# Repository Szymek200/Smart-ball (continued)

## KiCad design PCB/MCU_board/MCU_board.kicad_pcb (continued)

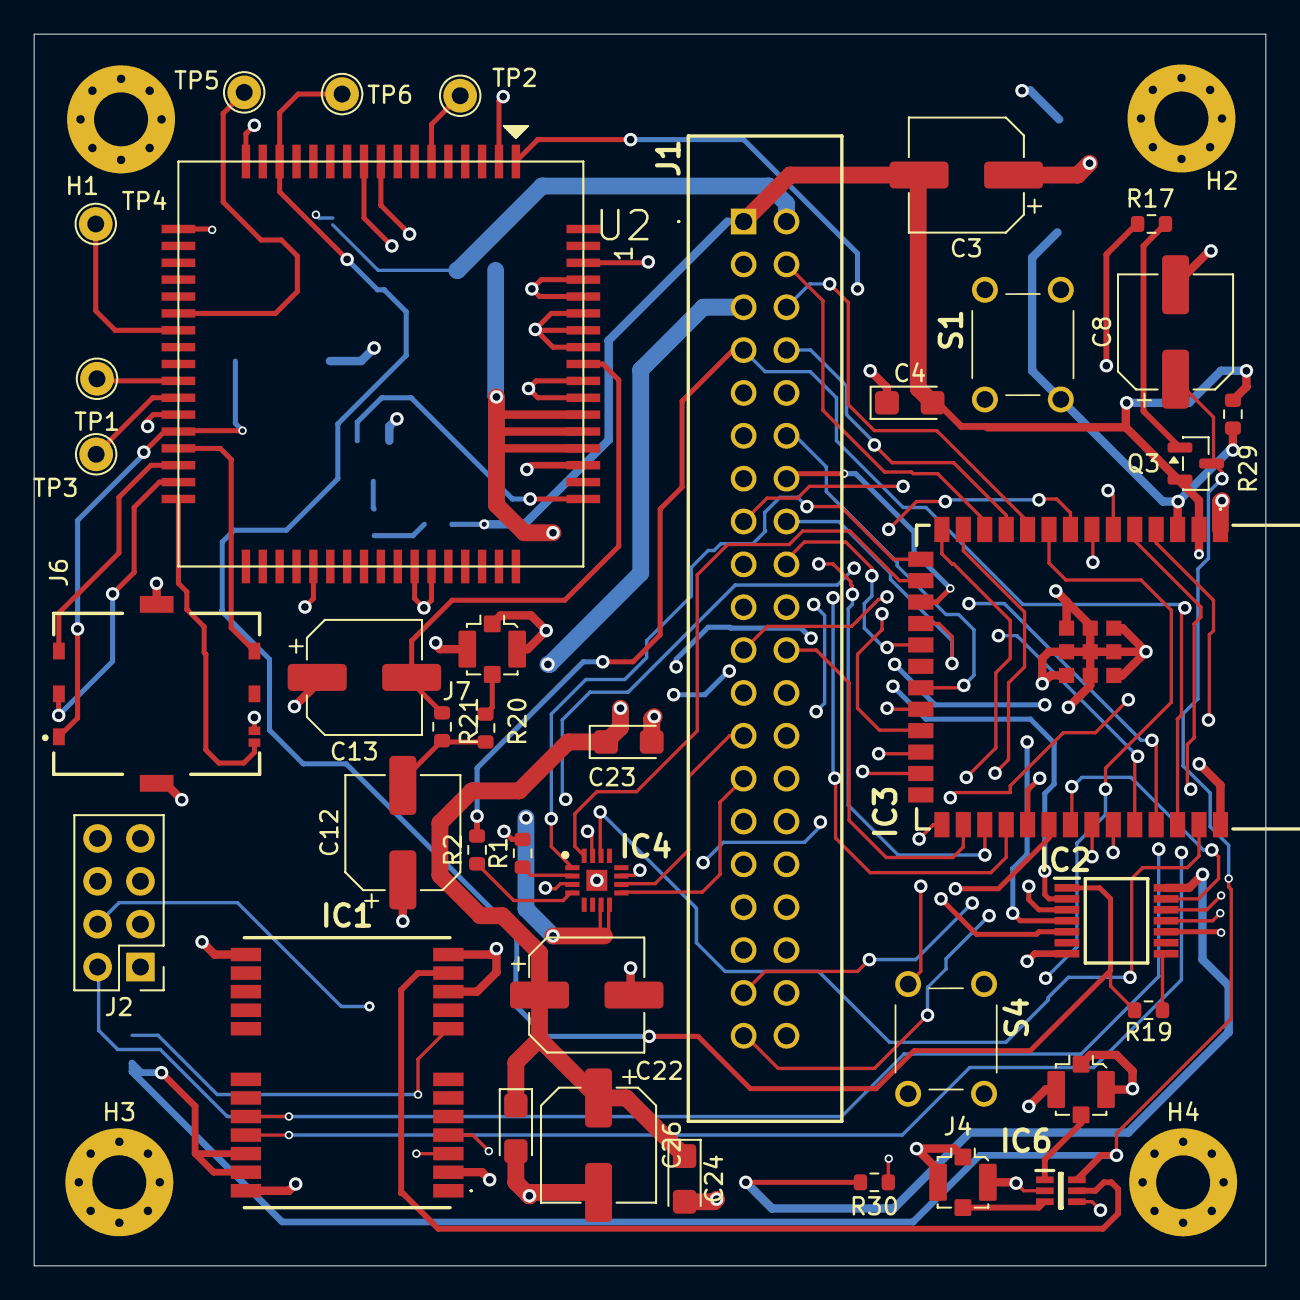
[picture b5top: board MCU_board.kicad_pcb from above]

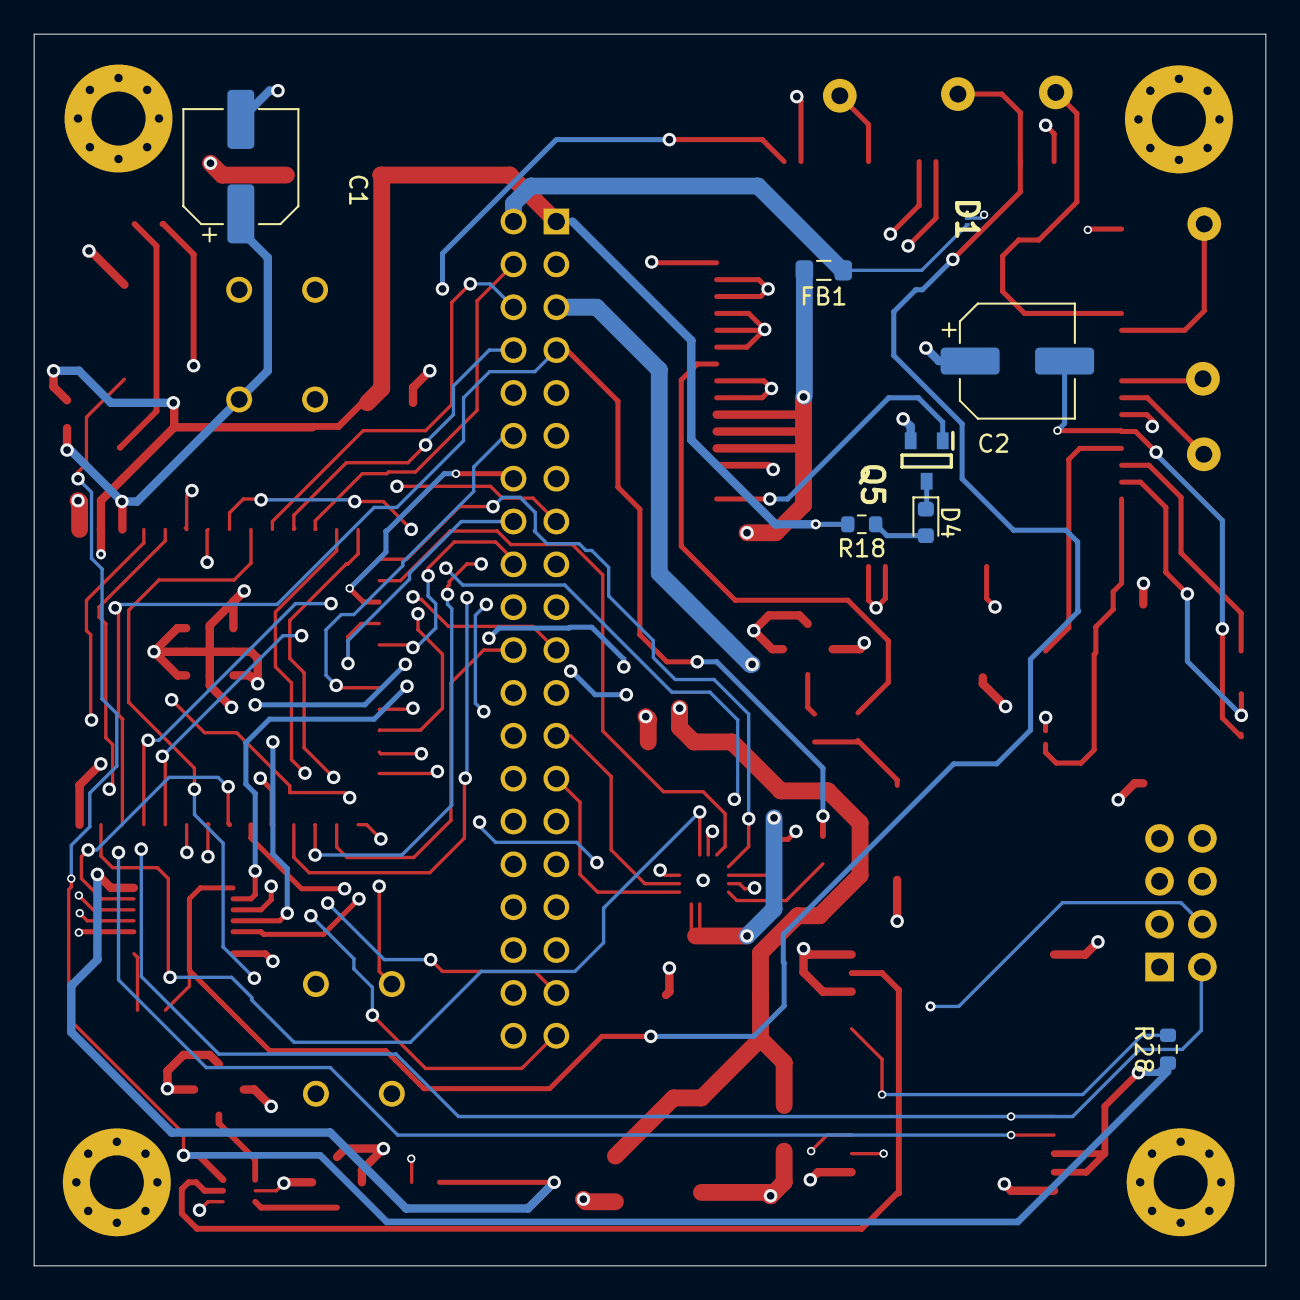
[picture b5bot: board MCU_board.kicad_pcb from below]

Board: 4 copper layers, 73.0 x 73.0 mm, 51 parts (8 on the bottom side), 72 nets.

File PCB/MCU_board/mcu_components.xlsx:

Designator | Footprint | Quantity | Value | LCSC Part #
C1, C26 | C_Disc_D5.0mm_W2.5mm_P2.50mm | 2 | 1μF
C12, C13 | C_Disc_D5.0mm_W2.5mm_P2.50mm | 2 | 0F
C2, C3 | C_Disc_D5.0mm_W2.5mm_P2.50mm | 2 | 100nF
C22 | C_Disc_D5.0mm_W2.5mm_P2.50mm | 1 | 1000nF
C23 | CP_Radial_Tantal_D5.0mm_P2.50mm | 1 | 1000µF
C24, C25 | CP_Radial_Tantal_D5.0mm_P2.50mm | 2 | 100µF
C4 | CP_Radial_Tantal_D5.0mm_P2.50mm | 1 | 1μF
C8 | C_Disc_D5.0mm_W2.5mm_P2.50mm | 1 | 100 nF
D1 | PMEG3005AESFYL | 1 | PESD5V0C1BSFYL
D4 | D_DO-41_SOD81_P7.62mm_Horizontal | 1 | LED
FB1 | 805 | 1 | 280Ω
IC1 | NEOF10N00B | 1 | NEO-F10N-00B
IC2 | SOP65P640X120-14N | 1 | TXB0104PWR
IC3 | ESP32S3WROOM1N4R8 | 1 | ESP32-S3-WROOM-1-N4R8
IC6 | SOT65P210X110-6N | 1 | 4259-63
IC8 | QFN50P300X300X80-17N | 1 | MAX98357AETE+T
J1 | DS101340SSIB1B0 | 1 | DS1013-40SSIB1-B-0
J4 | U.FL_Molex_MCRF_73412-0110_Vertical | 1 | FXP612 (u.FL) 2
J5, J7 | U.FL_Molex_MCRF_73412-0110_Vertical | 2 | FXP612 (u.FL) 1
J6 | GCT_SIM8055-6-1-14-00-A | 1 | SIM8055-6-1-14-00-A
Q3 | SOT95P237X112-3N | 1 | Si2323DDS-T1-GE3
Q5 | SOT95P240X120-3N | 1 | BSS138
R16, R26 | R_Axial_DIN0207_L6.3mm_D2.5mm_P7.62mm_Horizontal | 2 | 100kΩ
R17, R19, R28, R29, R30 | R_Axial_DIN0207_L6.3mm_D2.5mm_P7.62mm_Horizontal | 5 | 10kΩ
R18 | R_Axial_DIN0207_L6.3mm_D2.5mm_P7.62mm_Horizontal | 1 | 330Ω
R20, R21 | R_Axial_DIN0207_L6.3mm_D2.5mm_P7.62mm_Horizontal | 2 | 0Ω
S1, S4 | 18259106 | 2 | 1825910-6
TP1 | TestPoint_THTPad_D2.0mm_Drill1.0mm | 1 | USB_DP
TP2 | TestPoint_THTPad_D2.0mm_Drill1.0mm | 1 | BOOT_CFG
TP3 | TestPoint_THTPad_D2.0mm_Drill1.0mm | 1 | USB_DM
TP4 | TestPoint_THTPad_D2.0mm_Drill1.0mm | 1 | USB_VBUS
TP5 | TestPoint_THTPad_D2.0mm_Drill1.0mm | 1 | MDM_LOG_TX
TP6 | TestPoint_THTPad_D2.0mm_Drill1.0mm | 1 | TestPoint
U2 | SIM7000G | 1 | SIM7000G

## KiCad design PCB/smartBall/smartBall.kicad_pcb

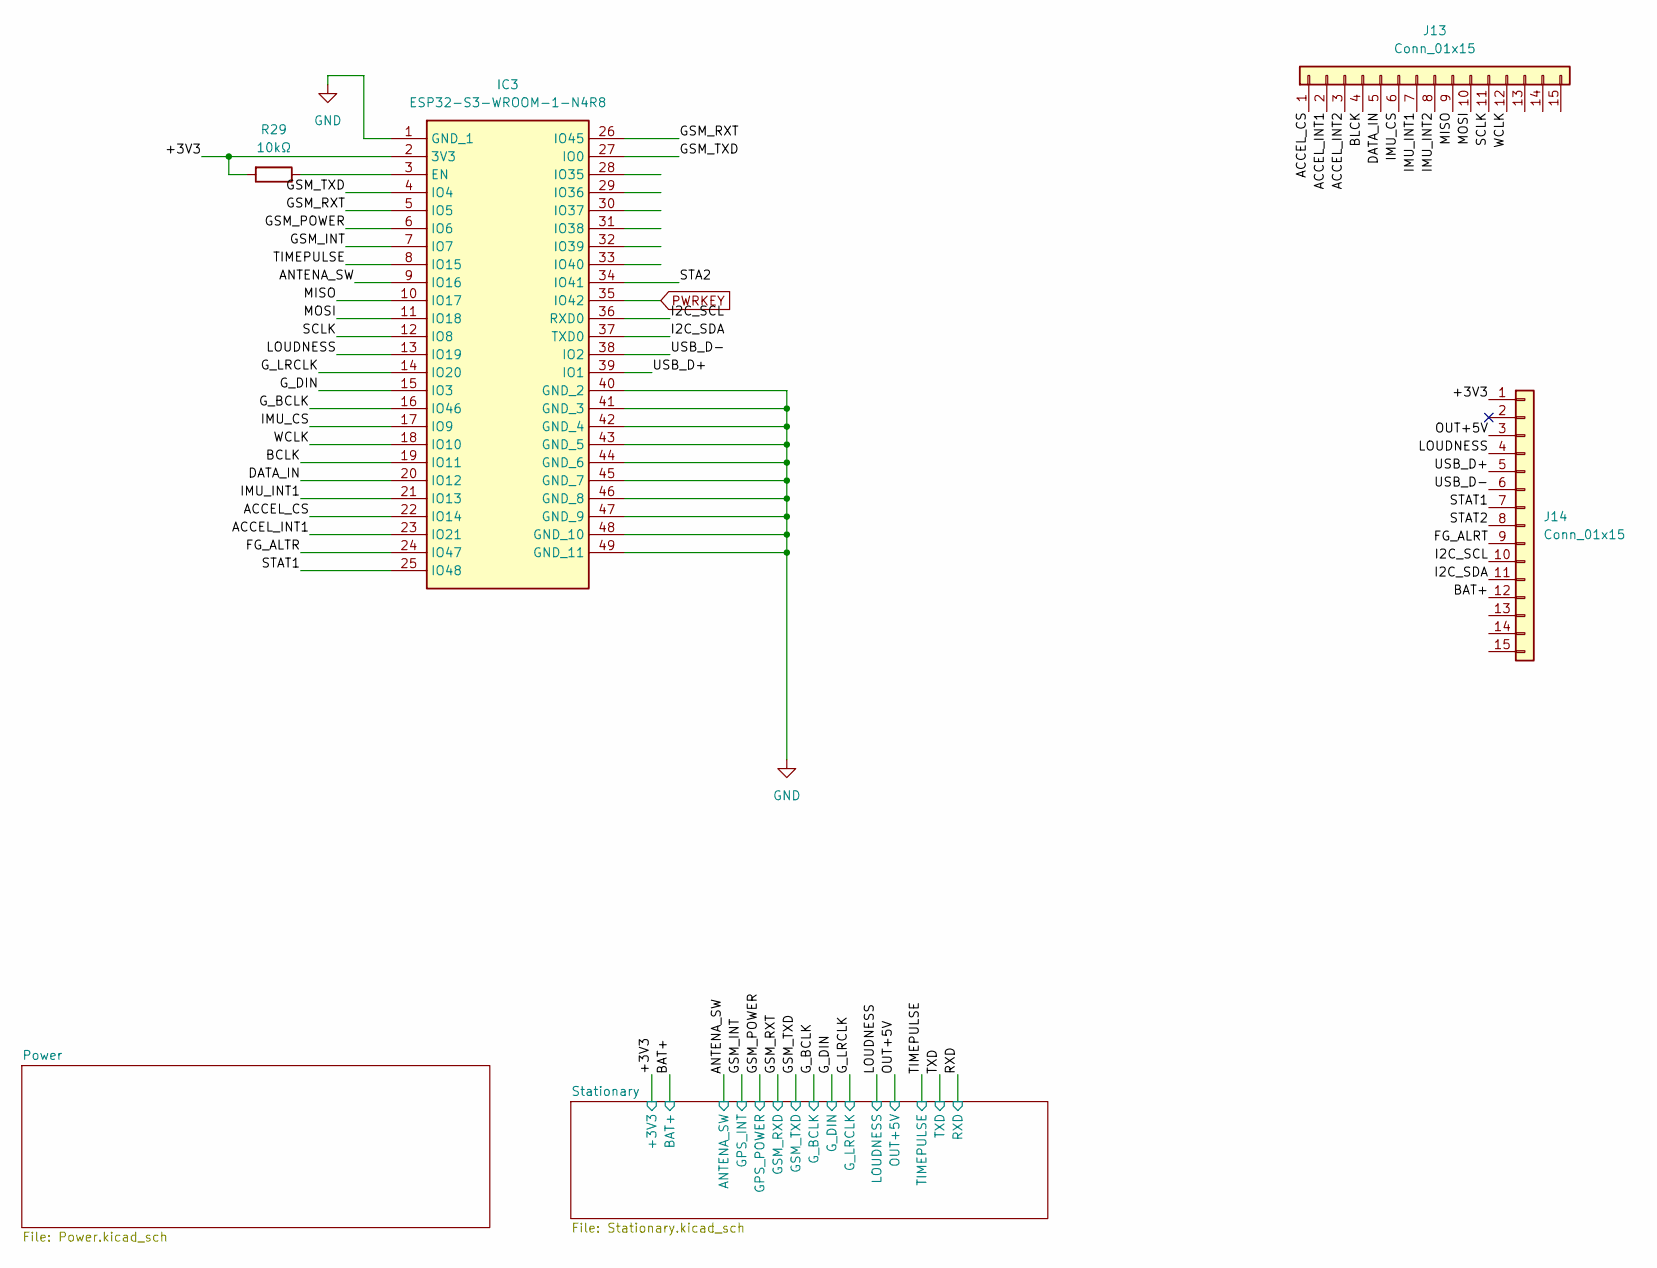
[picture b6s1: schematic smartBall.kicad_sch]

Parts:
IC3: ESP32-S3-WROOM-1-N4R8; ESP32S3WROOM1N4R8; Mouser Part Number 356-ESP32S3WROM1N4R8
J13, J14: Conn_01x15; PinHeader_1x15_P2.54mm_Vertical
R29: 10kΩ; R_Axial_DIN0207_L6.3mm_D2.5mm_P7.62mm_Horizontal

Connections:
/+3V3: IC3.2 (3V3), J14.1, R29.2; also elsewhere on the board
/ACCEL_CS: IC3.22 (IO14), J13.1
/ACCEL_INT1: IC3.23 (IO21), J13.2
/ACCEL_INT2: IC3.28 (IO35), J13.3
/ANTENA_SW: IC3.9 (IO16); also elsewhere on the board
/BAT+: J14.12
/DATA_IN: IC3.20 (IO12), J13.5
/GSM_INT: IC3.7 (IO7); also elsewhere on the board
/GSM_POWER: IC3.6 (IO6); also elsewhere on the board
/G_BCLK: IC3.16 (IO46); also elsewhere on the board
/G_DIN: IC3.15 (IO3); also elsewhere on the board
/G_LRCLK: IC3.14 (IO20); also elsewhere on the board
/I2C_SCL: IC3.36 (RXD0), J14.10
/I2C_SDA: IC3.37 (TXD0), J14.11
/IMU_CS: IC3.17 (IO9), J13.6
/IMU_INT1: IC3.21 (IO13), J13.7
/IMU_INT2: IC3.29 (IO36), J13.8
/LOUDNESS: IC3.13 (IO19), J14.4; also elsewhere on the board
/MISO: IC3.10 (IO17), J13.9
/MOSI: IC3.11 (IO18), J13.10
/OUT+5V: J14.3; also elsewhere on the board
/PWRKEY: IC3.31 (IO38); also elsewhere on the board
/SCLK: IC3.12 (IO8), J13.11
/STAT1: IC3.25 (IO48), J14.7
/STATUS: IC3.32 (IO39); also elsewhere on the board
/TIMEPULSE: IC3.8 (IO15); also elsewhere on the board
/TS/CTRL: IC3.30 (IO37), J14.2
/USB_D+: IC3.39 (IO1), J14.5
/USB_D-: IC3.38 (IO2), J14.6
/WCLK: IC3.18 (IO10), J13.12
GND: IC3.1 (GND_1), IC3.40 (GND_2), IC3.41 (GND_3), IC3.42 (GND_4), IC3.43 (GND_5), IC3.44 (GND_6), IC3.45 (GND_7), IC3.46 (GND_8), IC3.47 (GND_9), IC3.48 (GND_10), IC3.49 (GND_11); also elsewhere on the board
unnamed: IC3.3 (EN), R29.1

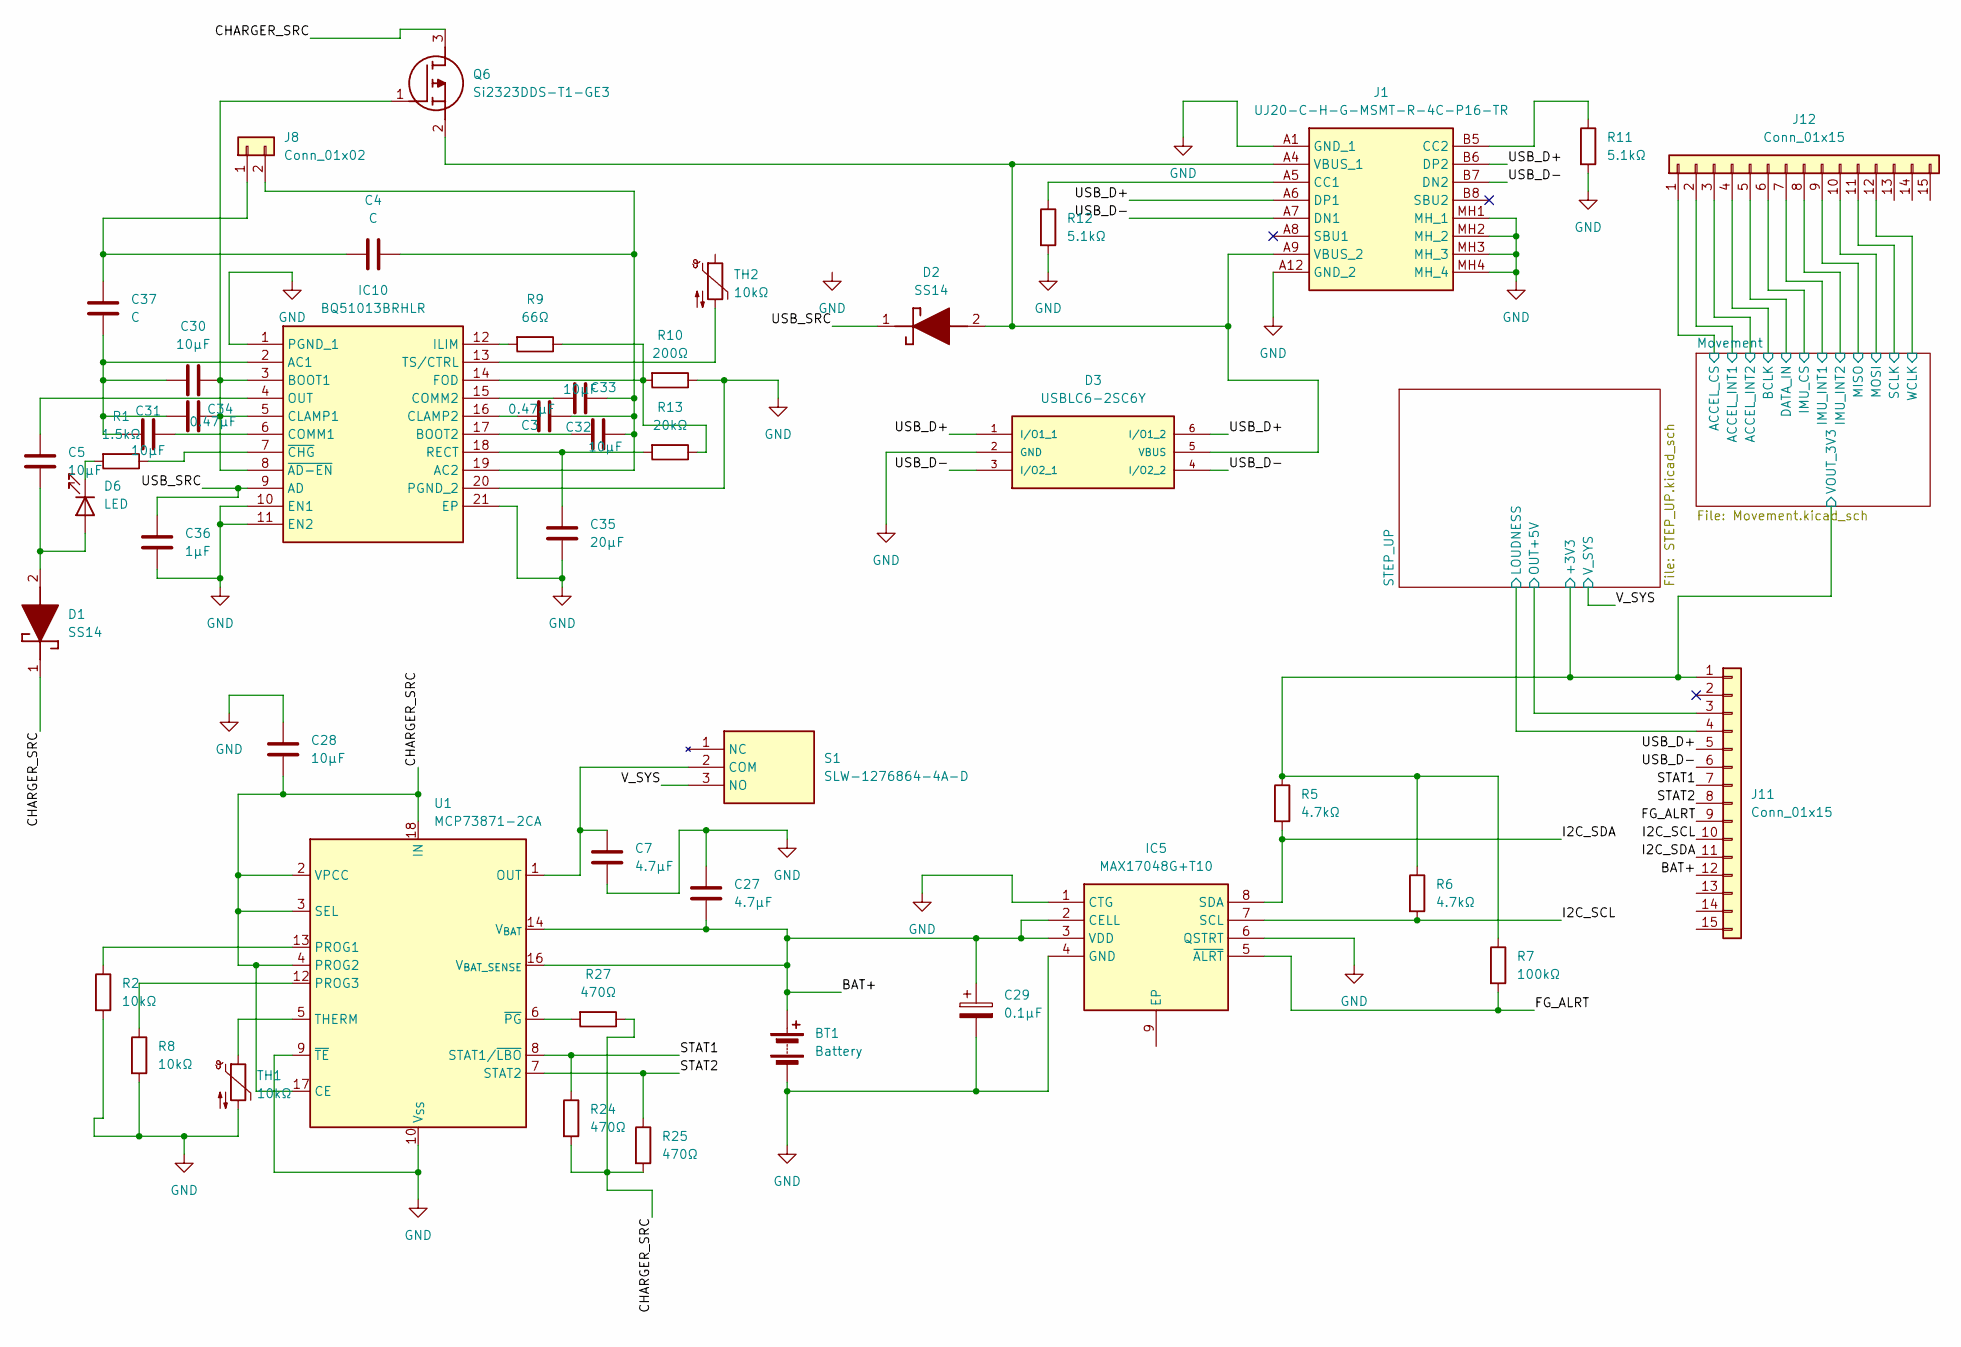
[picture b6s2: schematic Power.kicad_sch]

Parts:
BT1: Battery; SolderWire-0.75sqmm_1x02_P4.8mm_D1.25mm_OD2.3mm
C3, C34: 0.47µF; CP_Radial_Tantal_D5.0mm_P2.50mm
C4, C37: C; CP_Radial_Tantal_D5.0mm_P2.50mm
C5, C28, C30, C31, C32, C33: 10µF; CP_Radial_Tantal_D5.0mm_P2.50mm
C7, C27: 4.7µF; CP_Radial_Tantal_D5.0mm_P2.50mm
C29: 0.1µF; CP_Radial_Tantal_D5.0mm_P2.50mm
C35: 20µF; CP_Radial_Tantal_D5.0mm_P2.50mm
C36: 1µF; CP_Radial_Tantal_D5.0mm_P2.50mm
D1, D2: SS14; DIOM5227X270N; Mouser Part Number 512-SS14
D3: USBLC6-2SC6Y; SOT95P280X145-6N; MOUSER_PART_NUMBER 511-USBLC6-2SC6Y
D6: LED; D_DO-41_SOD81_P7.62mm_Horizontal
IC5: MAX17048G+T10; SON50P200X200X80-9N-D; Mouser Part Number 700-MAX17048G+T10
IC10: BQ51013BRHLR; BQ51050BRHLR; Mouser Part Number 595-BQ51013BRHLR
J1: UJ20-C-H-G-MSMT-R-4C-P16-TR; UJ20CHGMSMTR4CP16TR; Manufacturer_Part_Number UJ20-C-H-G-MSMT-R-4C-P16-TR
J8: Conn_01x02; PinHeader_1x02_P2.54mm_Vertical
J11, J12: Conn_01x15; PinHeader_1x15_P2.54mm_Vertical
Q6: Si2323DDS-T1-GE3; SOT95P237X112-3N; Mouser Part Number 78-SI2323DDS-T1-GE3
R1: 1.5kΩ; R_Axial_DIN0207_L6.3mm_D2.5mm_P7.62mm_Horizontal
R2, R8: 10kΩ; R_Axial_DIN0207_L6.3mm_D2.5mm_P7.62mm_Horizontal
R5, R6: 4.7kΩ; R_Axial_DIN0207_L6.3mm_D2.5mm_P7.62mm_Horizontal
R7: 100kΩ; R_Axial_DIN0207_L6.3mm_D2.5mm_P7.62mm_Horizontal
R9: 66Ω; R_Axial_DIN0207_L6.3mm_D2.5mm_P7.62mm_Horizontal
R10: 200Ω; R_Axial_DIN0207_L6.3mm_D2.5mm_P7.62mm_Horizontal
R11, R12: 5.1kΩ; R_Axial_DIN0207_L6.3mm_D2.5mm_P7.62mm_Horizontal
R13: 20kΩ; R_Axial_DIN0207_L6.3mm_D2.5mm_P7.62mm_Horizontal
R24, R25, R27: 470Ω; R_Axial_DIN0207_L6.3mm_D2.5mm_P7.62mm_Horizontal
S1: SLW-1276864-4A-D; SLW12768644AD; Mouser Part Number 179-SLW-1276864-4A-D
TH1, TH2: 10kΩ; R_Axial_DIN0207_L6.3mm_D2.5mm_P7.62mm_Horizontal
U1: MCP73871-2CA; QFN-20-1EP_4x4mm_P0.5mm_EP2.5x2.5mm

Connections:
/Power/BAT+: BT1.1 (+), C27.2, C29.1, IC5.2 (CELL), IC5.3 (VDD), J11.12, U1.14 (V_{BAT}), U1.15 (V_{BAT}), U1.16 (V_{BAT_SENSE})
/Power/CHARGER_SRC: C28.2, D1.1 (K), Q6.3 (D), R24.2, R25.2, R27.1, U1.2 (VPCC), U1.3 (SEL), U1.4 (PROG2), U1.17 (CE), U1.18 (IN), U1.19 (IN)
/Power/FG_ALRT: IC5.5 (~ALRT), J11.9, R7.2
/Power/I2C_SCL: IC5.7 (SCL), J11.10, R6.2
/Power/I2C_SDA: IC5.8 (SDA), J11.11, R5.2
/Power/Movement/ACCEL_CS: J12.1; also elsewhere on the board
/Power/Movement/ACCEL_INT1: J12.2; also elsewhere on the board
/Power/Movement/ACCEL_INT2: J12.3; also elsewhere on the board
/Power/Movement/BCLK: J12.4; also elsewhere on the board
/Power/Movement/DATA_IN: J12.5; also elsewhere on the board
/Power/Movement/IMU_CS: J12.6; also elsewhere on the board
/Power/Movement/IMU_INT1: J12.7; also elsewhere on the board
/Power/Movement/IMU_INT2: J12.8; also elsewhere on the board
/Power/Movement/MISO: J12.9; also elsewhere on the board
/Power/Movement/MOSI: J12.10; also elsewhere on the board
/Power/Movement/SCLK: J12.11; also elsewhere on the board
/Power/Movement/VOUT_3V3: J11.1, R5.1, R6.1, R7.1; also elsewhere on the board
/Power/Movement/WCLK: J12.12; also elsewhere on the board
/Power/STAT1: J11.7, R24.1, U1.8 (STAT1/~LBO)
/Power/STAT2: J11.8, R25.1, U1.7 (STAT2)
/Power/STEP_UP/LOUDNESS: J11.4; also elsewhere on the board
/Power/STEP_UP/OUT+5V: J11.3; also elsewhere on the board
/Power/USB_D+: D3.1 (I/O1_1), D3.6 (I/O1_2), J1.A6 (DP1), J1.B6 (DP2), J11.5
/Power/USB_D-: D3.3 (I/O2_1), D3.4 (I/O2_2), J1.A7 (DN1), J1.B7 (DN2), J11.6
/Power/USB_SRC: C36.1, D2.1 (K), IC10.9 (AD)
/Power/V_SYS: S1.3 (NO); also elsewhere on the board
GND: BT1.2 (-), C7.2, C27.1, C28.1, C29.2, C35.2, C36.2, D3.2 (GND), IC5.1 (CTG), IC5.4 (GND), IC5.6 (QSTRT), IC5.9 (EP), IC10.1 (PGND_1), IC10.10 (EN1), IC10.11 (EN2), IC10.20 (PGND_2), IC10.21 (EP), J1.A1 (GND_1), J1.A12 (GND_2), J1.MH1 (MH_1), J1.MH2 (MH_2), J1.MH3 (MH_3), J1.MH4 (MH_4), R2.2, R8.2, R10.1, R11.2, R12.2, TH1.2, TH2.1, U1.9 (~TE), U1.10 (V_{SS}), U1.11 (V_{SS}), U1.21 (V_{SS}); also elsewhere on the board
unnamed: C5.2, D1.2 (A), D6.2 (A)
unnamed: D2.2 (A), D3.5 (VBUS), J1.A4 (VBUS_1), J1.A9 (VBUS_2), Q6.2 (S)
unnamed: D6.1 (K), R1.2
unnamed: C30.2, C31.2, C34.2, C37.2, IC10.2 (AC1)
unnamed: C3.1, C4.1, C32.1, C33.1, IC10.19 (AC2), J8.2
unnamed: C30.1, C34.1, IC10.3 (BOOT1), IC10.5 (CLAMP1), IC10.8 (~AD-EN), Q6.1 (G)
unnamed: C32.2, IC10.17 (BOOT2)
unnamed: C3.2, IC10.16 (CLAMP2)
unnamed: C31.1, IC10.6 (COMM1)
unnamed: C33.2, IC10.15 (COMM2)
unnamed: IC10.14 (FOD), R9.1, R10.2, R13.1
unnamed: IC10.12 (ILIM), R9.2
unnamed: C5.1, IC10.4 (OUT)
unnamed: C35.1, IC10.18 (RECT), R13.2
unnamed: IC10.7 (~CHG), R1.1
unnamed: J1.A5 (CC1), R12.1
unnamed: J1.B5 (CC2), R11.1
unnamed: C4.2, C37.1, J8.1
unnamed: C7.1, S1.2 (COM), U1.1 (OUT), U1.20 (OUT)
unnamed: R2.1, U1.13 (PROG1)
unnamed: R8.1, U1.12 (PROG3)
unnamed: TH1.1, U1.5 (THERM)
unnamed: R27.2, U1.6 (~PG)

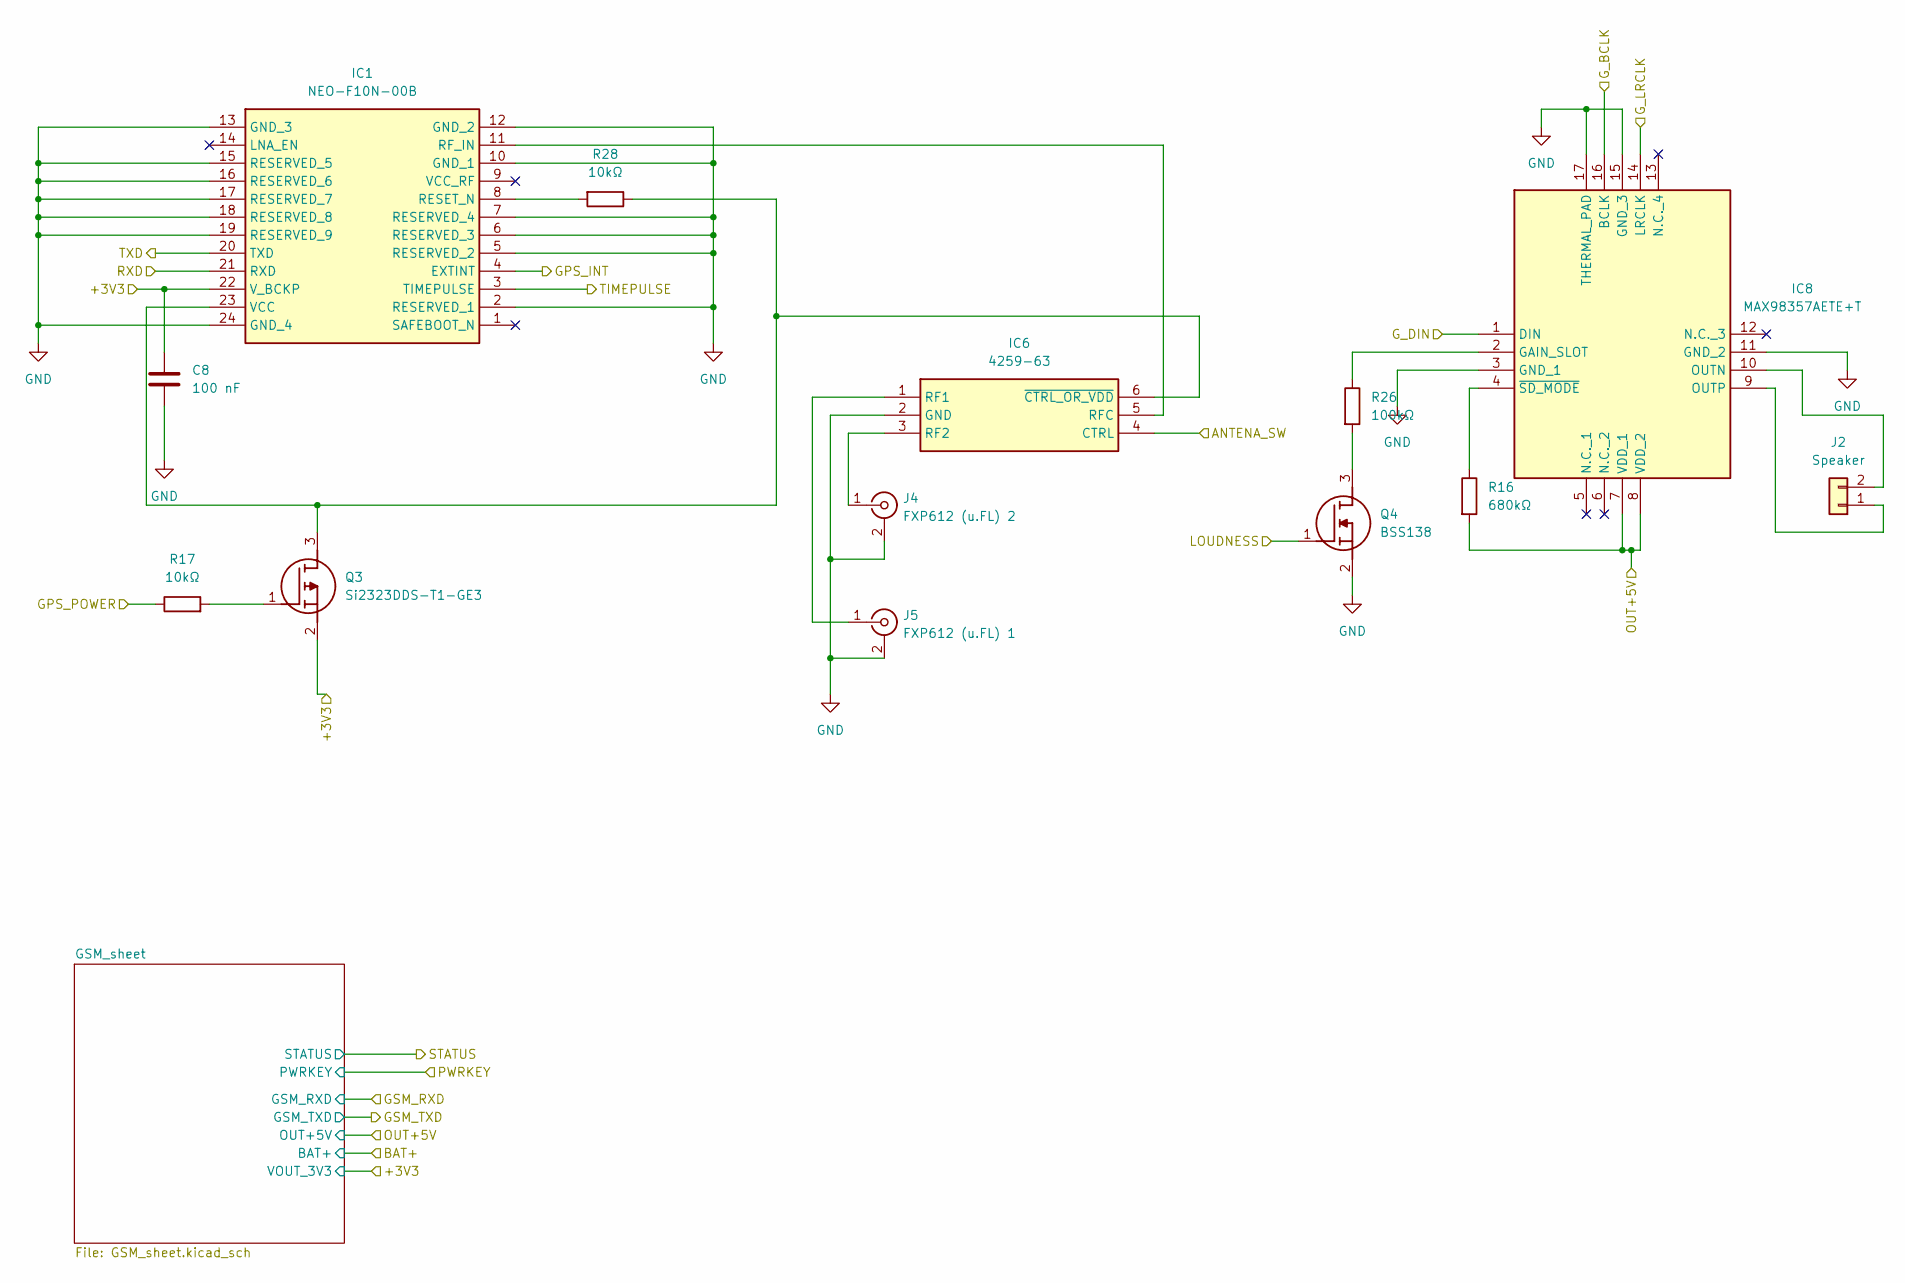
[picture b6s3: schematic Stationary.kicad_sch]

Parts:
C8: 100 nF; C_Disc_D5.0mm_W2.5mm_P2.50mm
IC1: NEO-F10N-00B; NEOF10N00B; Mouser Part Number 377-NEO-F10N-00B
IC6: 4259-63; SOT65P210X110-6N; Mouser Part Number 81-4259-63
IC8: MAX98357AETE+T; QFN50P300X300X80-17N; Mouser Part Number 700-MAX98357AETE+T
J2: Speaker; JST_PH_B2B-PH-K_1x02_P2.00mm_Vertical
J4: FXP612 (u.FL) 2; U.FL_Molex_MCRF_73412-0110_Vertical
J5: FXP612 (u.FL) 1; U.FL_Molex_MCRF_73412-0110_Vertical
Q3: Si2323DDS-T1-GE3; SOT95P237X112-3N; Mouser Part Number 78-SI2323DDS-T1-GE3
Q4: BSS138; SOT95P240X120-3N; Mouser Part Number 512-BSS138
R16: 680kΩ; R_Axial_DIN0207_L6.3mm_D2.5mm_P7.62mm_Horizontal
R17, R28: 10kΩ; R_Axial_DIN0207_L6.3mm_D2.5mm_P7.62mm_Horizontal
R26: 100kΩ; R_Axial_DIN0207_L6.3mm_D2.5mm_P7.62mm_Horizontal

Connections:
/+3V3: C8.1, IC1.22 (V_BCKP), Q3.2 (S); also elsewhere on the board
/ANTENA_SW: IC6.4 (CTRL); also elsewhere on the board
/GSM_INT: IC1.4 (EXTINT); also elsewhere on the board
/GSM_POWER: R17.1; also elsewhere on the board
/G_BCLK: IC8.16 (BCLK); also elsewhere on the board
/G_DIN: IC8.1 (DIN); also elsewhere on the board
/G_LRCLK: IC8.14 (LRCLK); also elsewhere on the board
/LOUDNESS: Q4.1 (G); also elsewhere on the board
/OUT+5V: IC8.7 (VDD_1), IC8.8 (VDD_2), R16.2; also elsewhere on the board
/TIMEPULSE: IC1.3 (TIMEPULSE); also elsewhere on the board
GND: C8.2, IC1.2 (RESERVED_1), IC1.5 (RESERVED_2), IC1.6 (RESERVED_3), IC1.7 (RESERVED_4), IC1.10 (GND_1), IC1.12 (GND_2), IC1.13 (GND_3), IC1.15 (RESERVED_5), IC1.16 (RESERVED_6), IC1.17 (RESERVED_7), IC1.18 (RESERVED_8), IC1.19 (RESERVED_9), IC1.24 (GND_4), IC6.2 (GND), IC8.3 (GND_1), IC8.11 (GND_2), IC8.15 (GND_3), IC8.17 (THERMAL_PAD), J4.2 (Ext), J5.2 (Ext), Q4.2 (S); also elsewhere on the board
unnamed: IC1.8 (RESET_N), R28.2
unnamed: IC1.11 (RF_IN), IC6.5 (RFC)
unnamed: IC1.23 (VCC), IC6.6 (~CTRL_OR_VDD), Q3.3 (D), R28.1
unnamed: IC6.1 (RF1), J5.1 (In)
unnamed: IC6.3 (RF2), J4.1 (In)
unnamed: IC8.2 (GAIN_SLOT), R26.1
unnamed: IC8.10 (OUTN), J2.2
unnamed: IC8.9 (OUTP), J2.1
unnamed: IC8.4 (~SD_MODE), R16.1
unnamed: Q3.1 (G), R17.2
unnamed: Q4.3 (D), R26.2

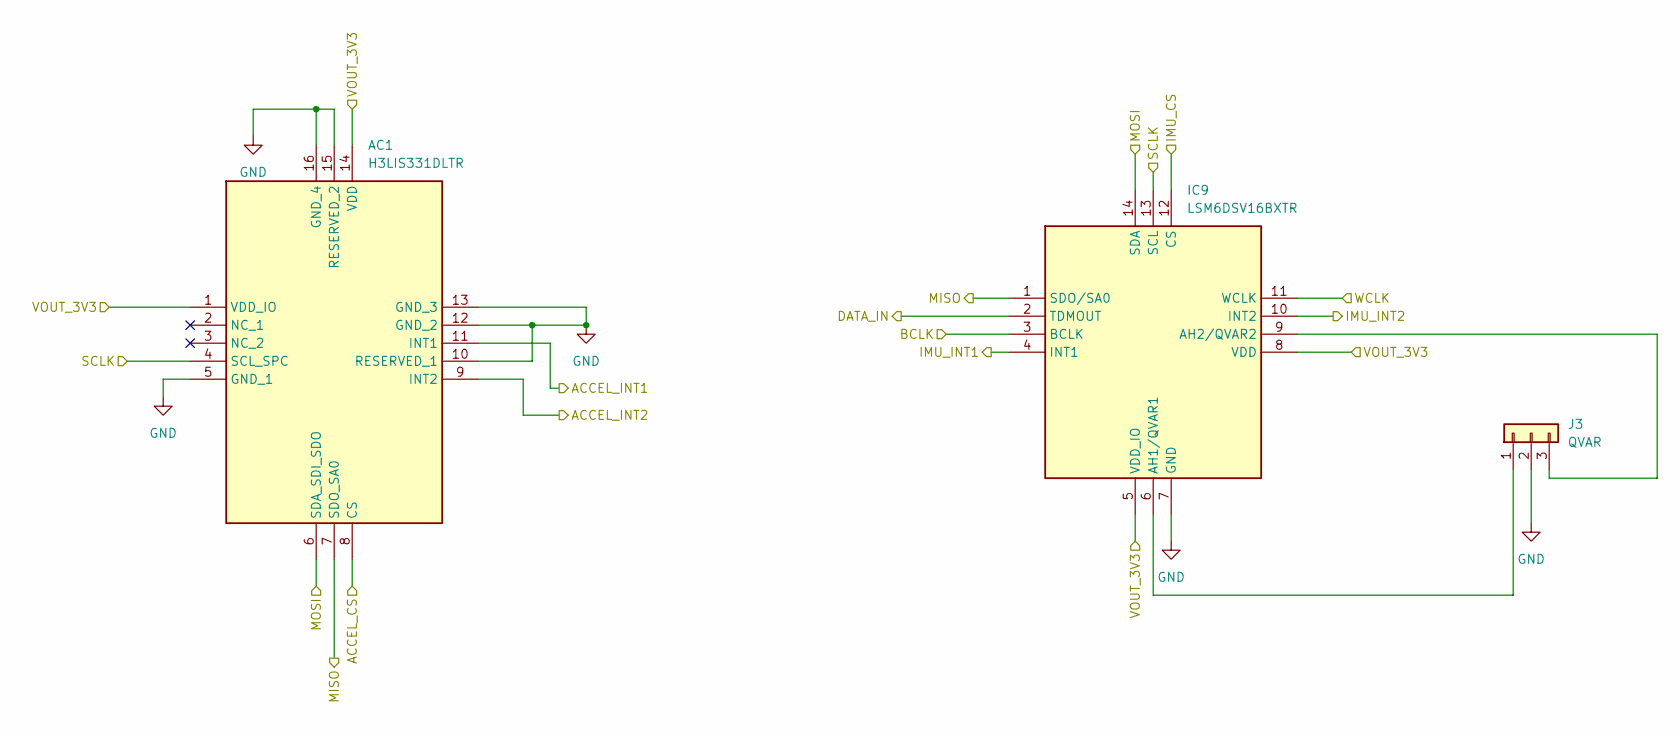
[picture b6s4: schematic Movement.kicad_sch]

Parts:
AC1: H3LIS331DLTR; LIS3DHTR; Mouser Part Number 511-H3LIS331DLTR
IC9: LSM6DSV16BXTR; Mouser Part Number 511-LSM6DSV16BXTR
J3: QVAR; JST_PH_B3B-PH-K_1x03_P2.00mm_Vertical

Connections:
/Power/Movement/ACCEL_CS: AC1.8 (CS); also elsewhere on the board
/Power/Movement/ACCEL_INT1: AC1.11 (INT1); also elsewhere on the board
/Power/Movement/ACCEL_INT2: AC1.9 (INT2); also elsewhere on the board
/Power/Movement/BCLK: IC9.3 (BCLK); also elsewhere on the board
/Power/Movement/DATA_IN: IC9.2 (TDMOUT); also elsewhere on the board
/Power/Movement/IMU_CS: IC9.12 (CS); also elsewhere on the board
/Power/Movement/IMU_INT1: IC9.4 (INT1); also elsewhere on the board
/Power/Movement/IMU_INT2: IC9.10 (INT2); also elsewhere on the board
/Power/Movement/MISO: AC1.7 (SDO_SA0), IC9.1 (SDO/SA0); also elsewhere on the board
/Power/Movement/MOSI: AC1.6 (SDA_SDI_SDO), IC9.14 (SDA); also elsewhere on the board
/Power/Movement/SCLK: AC1.4 (SCL_SPC), IC9.13 (SCL); also elsewhere on the board
/Power/Movement/VOUT_3V3: AC1.1 (VDD_IO), AC1.14 (VDD), IC9.5 (VDD_IO), IC9.8 (VDD); also elsewhere on the board
/Power/Movement/WCLK: IC9.11 (WCLK); also elsewhere on the board
GND: AC1.5 (GND_1), AC1.10 (RESERVED_1), AC1.12 (GND_2), AC1.13 (GND_3), AC1.15 (RESERVED_2), AC1.16 (GND_4), IC9.7 (GND), J3.2; also elsewhere on the board
unnamed: IC9.6 (AH1/QVAR1), J3.1
unnamed: IC9.9 (AH2/QVAR2), J3.3

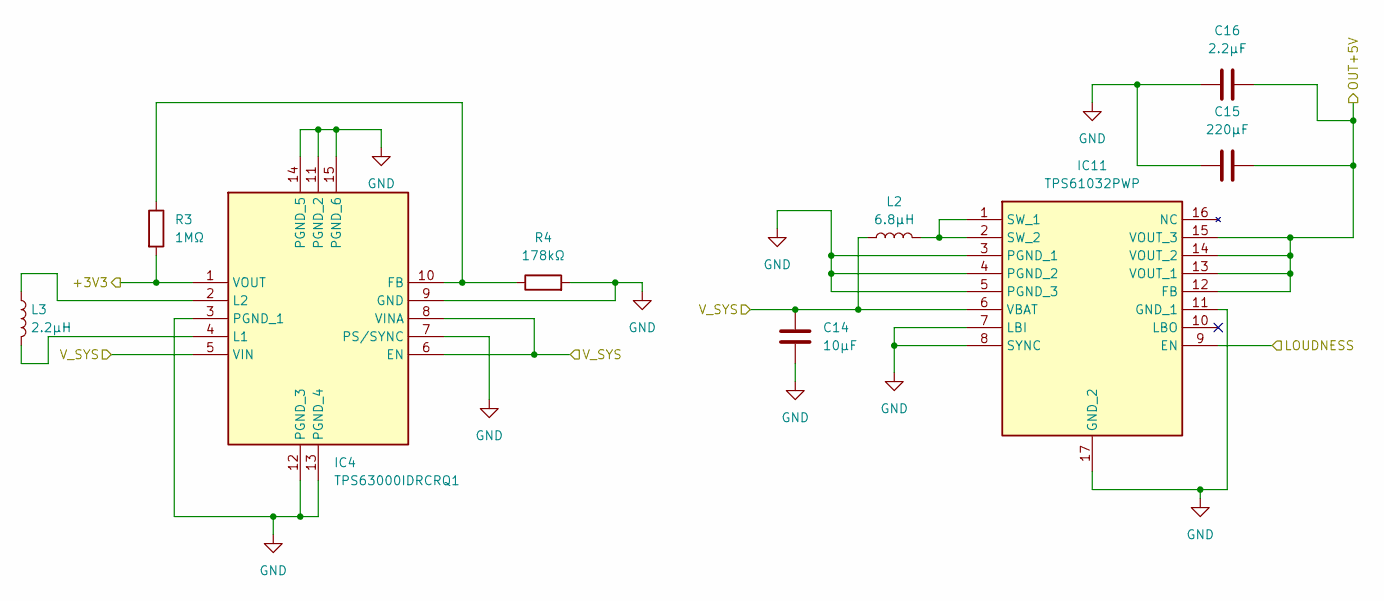
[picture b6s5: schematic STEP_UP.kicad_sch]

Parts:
C14: 10µF; C_Disc_D5.0mm_W2.5mm_P2.50mm
C15: 220µF; C_Disc_D5.0mm_W2.5mm_P2.50mm
C16: 2.2µF; C_Disc_D5.0mm_W2.5mm_P2.50mm
IC4: TPS63000IDRCRQ1; Mouser Part Number 595-TPS63000IDRCRQ1
IC11: TPS61032PWP; SOP65P640X120-17N; Mouser Part Number 595-TPS61032PWP
L2: 6.8µH; L_Axial_L7.0mm_D3.3mm_P10.16mm_Horizontal_Fastron_MICC
L3: 2.2µH; L_Axial_L7.0mm_D3.3mm_P10.16mm_Horizontal_Fastron_MICC
R3: 1MΩ; R_Axial_DIN0207_L6.3mm_D2.5mm_P7.62mm_Horizontal
R4: 178kΩ; R_Axial_DIN0207_L6.3mm_D2.5mm_P7.62mm_Horizontal

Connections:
/Power/Movement/VOUT_3V3: IC4.1 (VOUT), R3.2; also elsewhere on the board
/Power/STEP_UP/LOUDNESS: IC11.9 (EN); also elsewhere on the board
/Power/STEP_UP/OUT+5V: C15.1, C16.2, IC11.12 (FB), IC11.13 (VOUT_1), IC11.14 (VOUT_2), IC11.15 (VOUT_3); also elsewhere on the board
/Power/V_SYS: C14.1, IC4.5 (VIN), IC4.6 (EN), IC4.8 (VINA), IC11.6 (VBAT), L2.1; also elsewhere on the board
GND: C14.2, C15.2, C16.1, IC4.3 (PGND_1), IC4.7 (PS/SYNC), IC4.9 (GND), IC4.11 (PGND_2), IC4.12 (PGND_3), IC4.13 (PGND_4), IC4.14 (PGND_5), IC4.15 (PGND_6), IC11.3 (PGND_1), IC11.4 (PGND_2), IC11.5 (PGND_3), IC11.7 (LBI), IC11.8 (SYNC), IC11.11 (GND_1), IC11.17 (GND_2), R4.2; also elsewhere on the board
unnamed: IC4.10 (FB), R3.1, R4.1
unnamed: IC4.4 (L1), L3.2
unnamed: IC4.2 (L2), L3.1
unnamed: IC11.1 (SW_1), IC11.2 (SW_2), L2.2
